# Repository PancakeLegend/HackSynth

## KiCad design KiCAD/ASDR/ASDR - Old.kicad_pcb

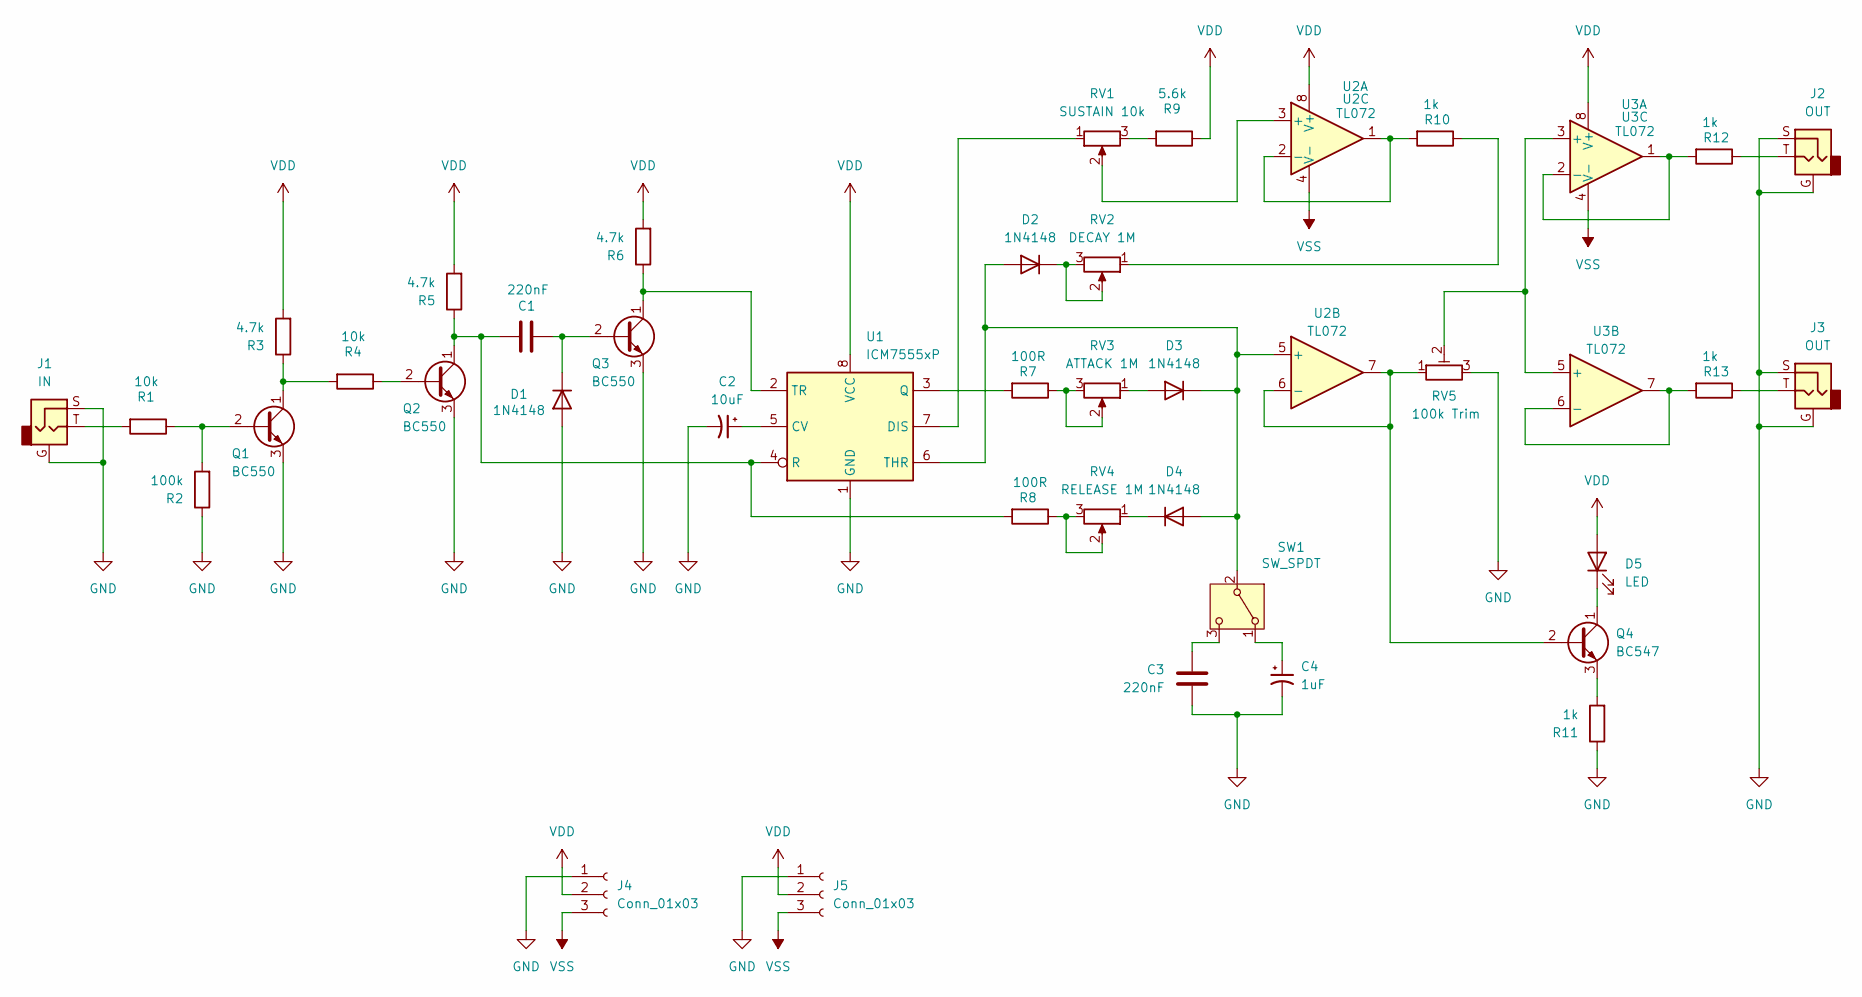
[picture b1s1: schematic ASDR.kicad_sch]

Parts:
C1, C3: 220nF; C_Ceramic_D4.5mm_P5.00mm
C2: 10uF; CP_Radial_D5.2mm_P2.50mm_LayDown
C4: 1uF; C_Ceramic_D4.5mm_P5.00mm
D1, D2, D3, D4: 1N4148; D_DO-35_SOD27_P7.62mm_Horizontal
D5: LED; LED_D5.0mm
J1: IN; Jack_3.5mm
J2, J3: OUT; Jack_3.5mm
J4, J5: Conn_01x03; JST_PH_S3B-PH-K_1x03_P2.00mm_Horizontal
Q1, Q2, Q3: BC550; TO-92_Inline - Handsolder
Q4: BC547; TO-92_Inline - Handsolder
R1, R4: 10k; R_Axial_DIN0207_L6.3mm_D2.5mm_P7.62mm_Horizontal
R2: 100k; R_Axial_DIN0207_L6.3mm_D2.5mm_P7.62mm_Horizontal
R3, R5, R6: 4.7k; R_Axial_DIN0207_L6.3mm_D2.5mm_P7.62mm_Horizontal
R7, R8: 100R; R_Axial_DIN0207_L6.3mm_D2.5mm_P7.62mm_Horizontal
R9: 5.6k; R_Axial_DIN0207_L6.3mm_D2.5mm_P7.62mm_Horizontal
R10, R11, R12, R13: 1k; R_Axial_DIN0207_L6.3mm_D2.5mm_P7.62mm_Horizontal
RV1: SUSTAIN 10k; Potentiometer_Alps_RK09K_Horizontal
RV2: DECAY 1M; Potentiometer_Alps_RK09K_Horizontal
RV3: ATTACK 1M; Potentiometer_Alps_RK09K_Horizontal
RV4: RELEASE 1M; Potentiometer_Alps_RK09K_Horizontal
RV5: 100k Trim; TrimPot_Bourns_3339S_Horizontal
SW1: SW_SPDT; Switch SPDT - MTS-102
U1: ICM7555xP; DIP-8_W7.62mm_LongPads
U2, U3: TL072; DIP-8_W7.62mm_LongPads

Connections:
GND: C2.2, C3.2, C4.2, D1.2 (A), J1.G, J1.S, J2.G, J2.S, J3.G, J3.S, J4.1, J5.1, Q1.3 (E), Q2.3 (E), Q3.3 (E), R2.1, R11.1, RV5.3, U1.1 (GND)
unnamed: C1.1, D1.1 (K), Q3.2 (B)
unnamed: D2.2 (A), D3.1 (K), D4.2 (A), SW1.2 (B), U1.6 (THR), U2.5 (+)
unnamed: D2.1 (K), RV2.2, RV2.3
unnamed: D3.2 (A), RV3.1
unnamed: D4.1 (K), RV4.1
unnamed: D5.1 (K), Q4.1 (C)
unnamed: J1.T, R1.2
unnamed: J2.T, R12.1
unnamed: J3.T, R13.1
unnamed: Q1.2 (B), R1.1, R2.2
unnamed: Q1.1 (C), R3.1, R4.2
unnamed: Q2.2 (B), R4.1
unnamed: C1.2, Q2.1 (C), R5.1, R8.2, U1.4 (R)
unnamed: Q3.1 (C), R6.1, U1.2 (TR)
unnamed: Q4.2 (B), RV5.1, U2.6 (-), U2.7
unnamed: Q4.3 (E), R11.2
unnamed: R7.1, RV3.2, RV3.3
unnamed: R8.1, RV4.2, RV4.3
unnamed: R9.2, RV1.3
unnamed: R10.1, RV2.1
unnamed: C4.1, SW1.1 (A)
unnamed: C3.1, SW1.3 (C)
unnamed: C2.1, U1.5 (CV)
unnamed: RV1.1, U1.7 (DIS)
unnamed: R7.2, U1.3 (Q)
unnamed: RV1.2, U2.3 (+)
unnamed: R10.2, U2.1, U2.2 (-)
unnamed: RV5.2, U3.3 (+), U3.5 (+)
unnamed: R12.2, U3.1, U3.2 (-)
unnamed: R13.2, U3.6 (-), U3.7
VDD: D5.2 (A), J4.2, J5.2, R3.2, R5.2, R6.2, R9.1, U1.8 (VCC), U2.8 (V+), U3.8 (V+)
VSS: J4.3, J5.3, U2.4 (V-), U3.4 (V-)

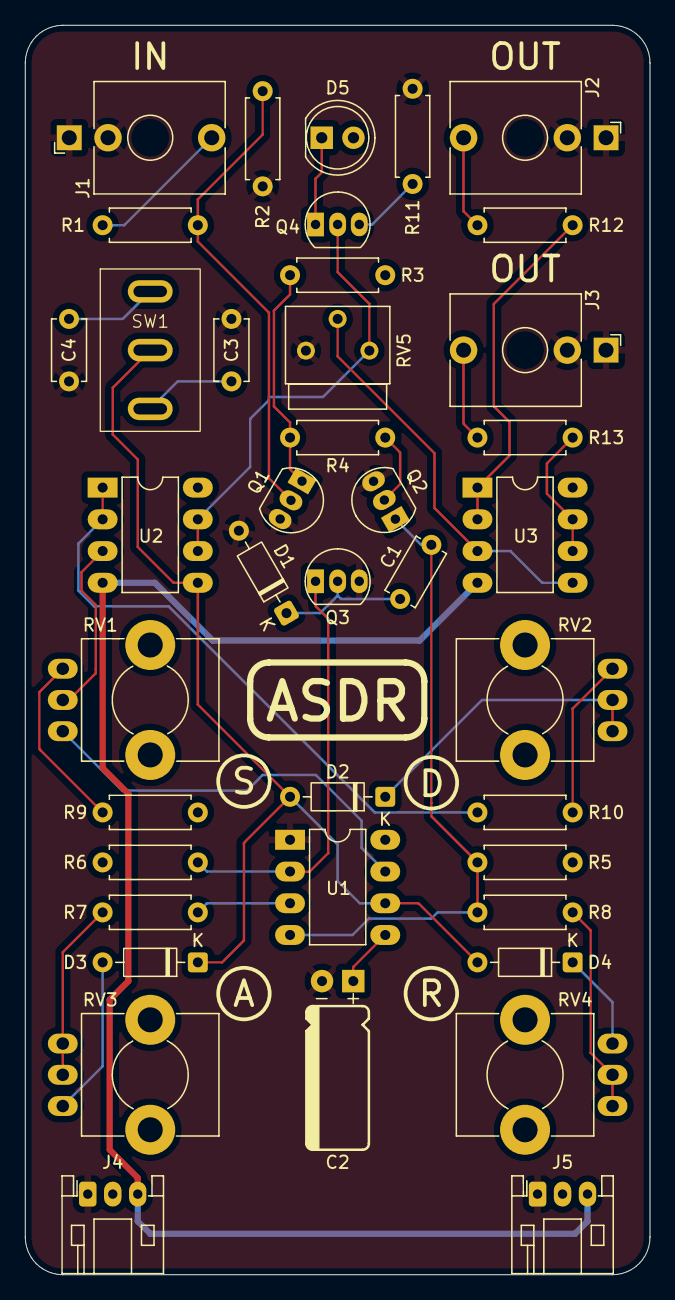
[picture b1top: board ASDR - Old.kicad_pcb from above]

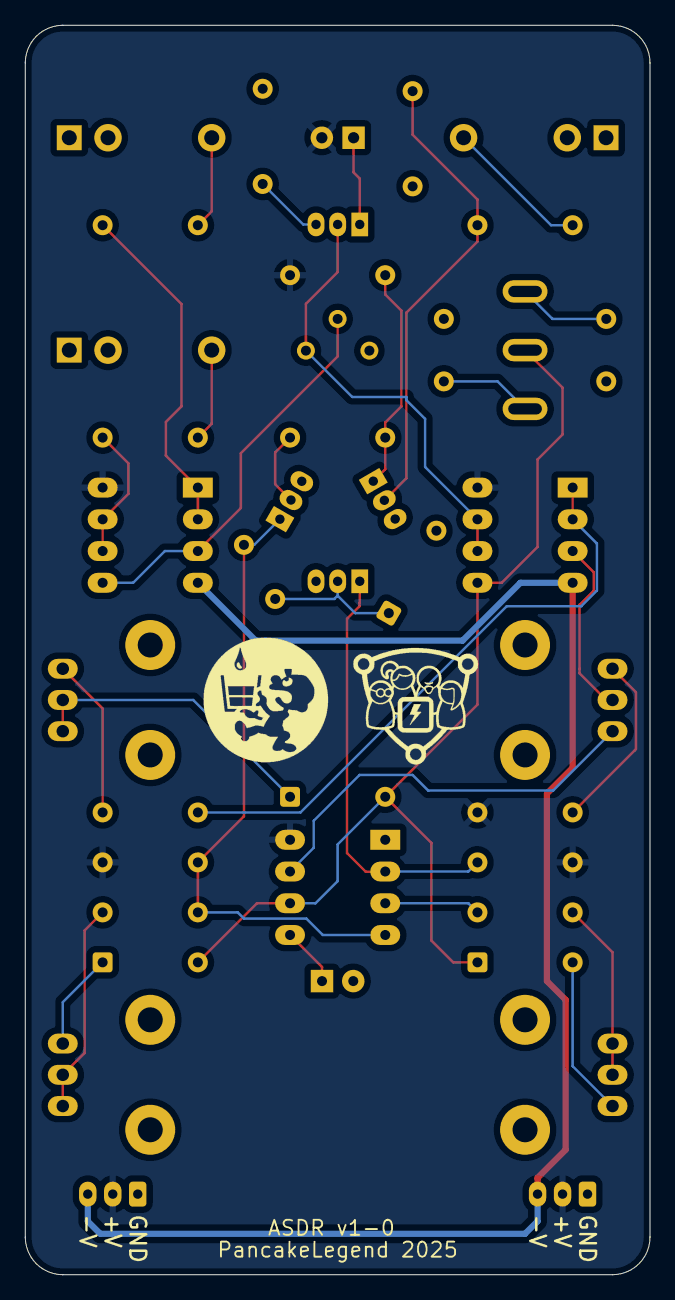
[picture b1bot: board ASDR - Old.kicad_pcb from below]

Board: 2 copper layers, 50.0 x 100.0 mm, 42 parts (2 on the bottom side), 33 nets.

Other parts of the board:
Ref**: Val**; CCHS Logo - 10mm
Ref**#2: Val**; PancakeLegend Logo - 10mm

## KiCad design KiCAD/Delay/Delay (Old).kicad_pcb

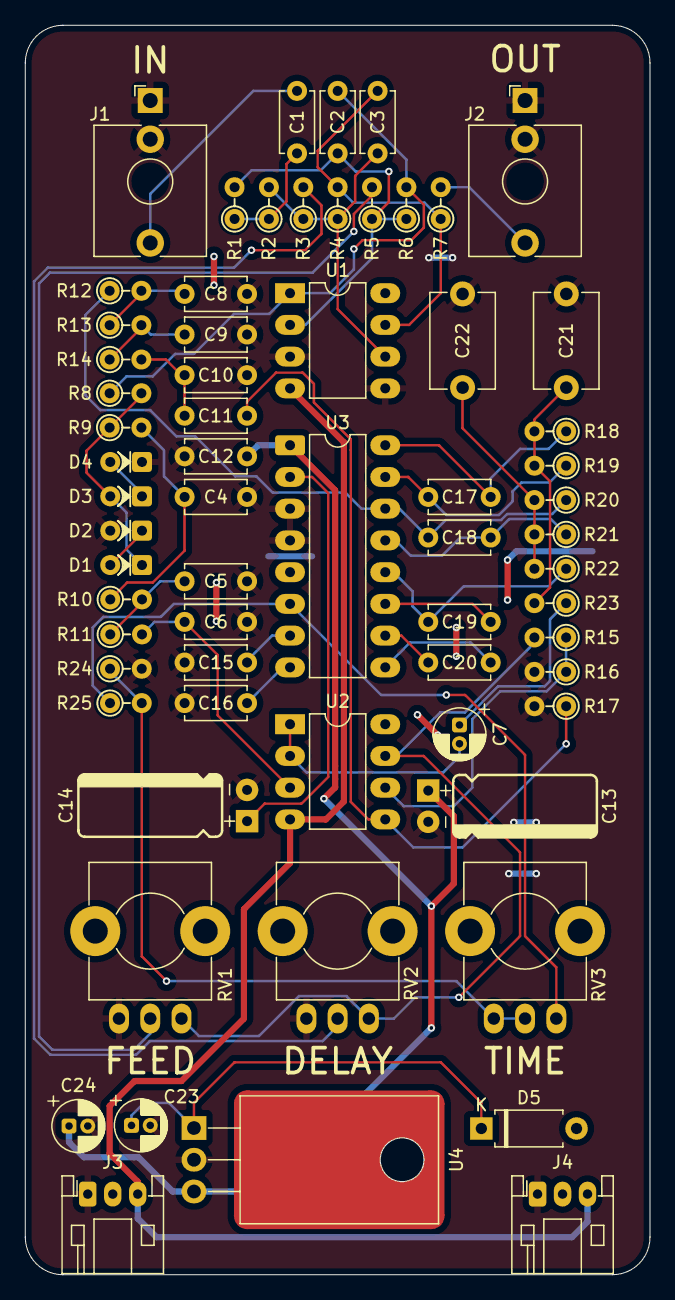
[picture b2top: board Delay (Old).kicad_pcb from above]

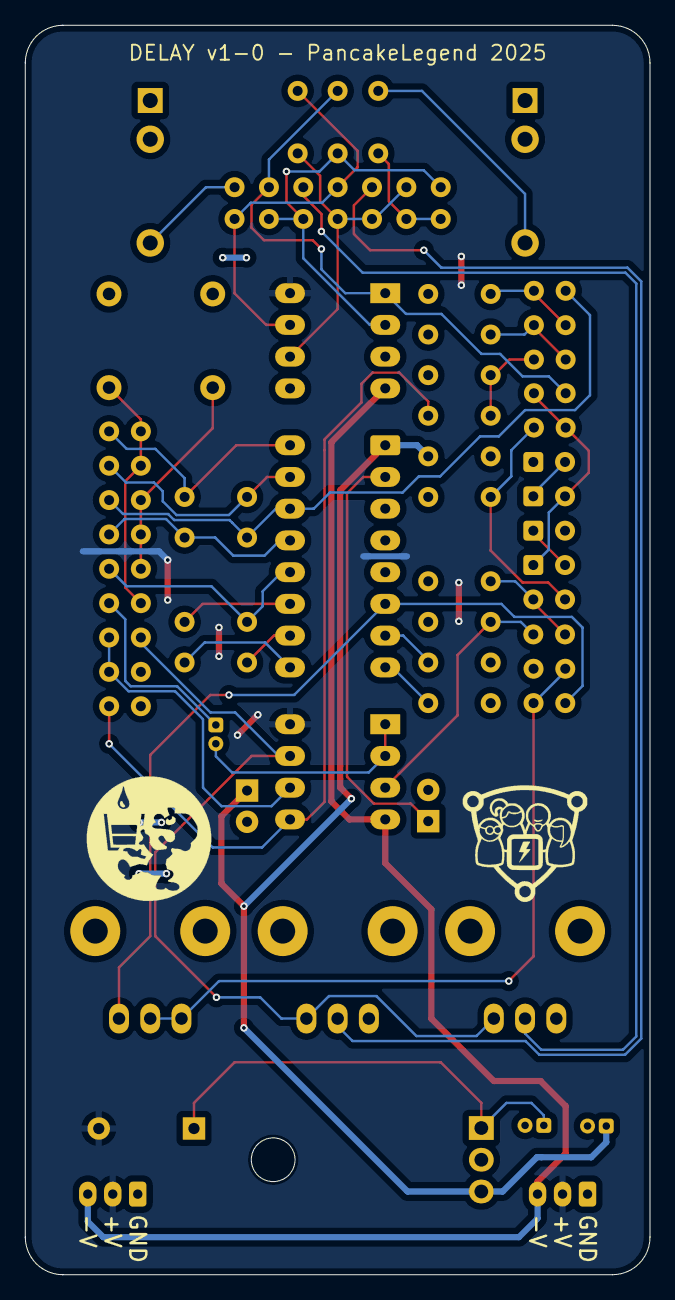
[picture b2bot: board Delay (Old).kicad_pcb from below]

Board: 2 copper layers, 50.0 x 100.0 mm, 67 parts (2 on the bottom side), 43 nets.

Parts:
C1: 220nF; C_Ceramic_D4.5mm_P5.00mm
C2, C3: 68pF; C_Ceramic_D4.5mm_P5.00mm
C4, C8: 2.2nF; C_Ceramic_D4.5mm_P5.00mm
C5, C9: 680pF; C_Ceramic_D4.5mm_P5.00mm
C6, C10: 220pF; C_Ceramic_D4.5mm_P5.00mm
C7: 1uF; CP_Radial_D4.0mm_P1.50mm
C11: 10nF; C_Ceramic_D4.5mm_P5.00mm
C12, C15, C16: 100nF; C_Ceramic_D4.5mm_P5.00mm
C13: 100µF; CP_Radial_D5.2mm_P2.50mm_LayDown
C14: 47µF; CP_Radial_D5.2mm_P2.50mm_LayDown
C17, C18: 560pF; C_Ceramic_D4.5mm_P5.00mm
C19, C20: 22nF; C_Ceramic_D4.5mm_P5.00mm
C21: 6.8nF; C_Disc_D7.5mm_W5.0mm_P7.50mm
C22: 3.3nF; C_Disc_D7.5mm_W5.0mm_P7.50mm
C23: 10uF 25v; CP_Radial_D4.0mm_P1.50mm
C24: 1uF 50v; CP_Radial_D4.0mm_P1.50mm
D1, D2, D3, D4: 1N4148; D_Vertical_P2.54mm
D5: 1N4002; D_A-405_P7.62mm_Horizontal
J1: IN; Jack_3.5mm
J2: OUT; Jack_3.5mm
J3, J4: Conn_01x03; JST_PH_S3B-PH-K_1x03_P2.00mm_Horizontal
R1, R2, R3, R5, R11, R14, R15: 100k; R_Vertical_P2.54mm
R4, R6, R19, R20, R22, R23: 22k; R_Vertical_P2.54mm
R7, R8, R24: 1k; R_Vertical_P2.54mm
R9, R12, R18, R21: 10k; R_Vertical_P2.54mm
R10, R13: 33k; R_Vertical_P2.54mm
R16: 56k; R_Vertical_P2.54mm
R17: 1M; R_Vertical_P2.54mm
R25: 68k; R_Vertical_P2.54mm
RV1, RV2: 10k; Potentiometer_Alps_RK09K_Horizontal
RV3: 47k; Potentiometer_Alps_RK09K_Horizontal
Ref**: Val**; CCHS Logo - 10mm
Ref**#2: Val**; PancakeLegend Logo - 10mm
U1, U2: TL072; DIP-8_W7.62mm_LongPads
U3: PT2399; DIP-16_W7.62mm_LongPads
U4: L7805; L7805 - TO-220-3_Horizontal_TabDown

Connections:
+5V: C12.1, C13.1, C24.1, U3.1 (VCC), U4.3 (OUT)
D IN: C7.1, R23.1
D OUT: C18.1, R12.1, R20.1, U3.14 (LPF2-OUT)
DELAY: R3.2, RV2.2
FEEDBACK: R5.2, RV1.2
GND: C4.2, C5.2, C6.2, C8.2, C9.2, C10.2, C12.2, C13.2, C14.2, C15.2, C16.2, C21.1, C22.1, C23.2, C24.2, D2.1 (K), D4.2 (A), J1.G, J1.S, J2.G, J2.S, J3.1, J4.1, R16.2, R17.2, R24.2, RV1.3, RV2.3, U1.3 (+), U1.5 (+), U3.3 (AGND), U3.4 (DGND), U4.2 (GND)
unnamed: C1.1, R1.1, R2.1
unnamed: C1.2, J1.T
unnamed: C2.1, R6.2, R8.1, U1.1
unnamed: C3.1, R4.2, R7.1, U1.7
unnamed: C4.1, R9.2, R10.1
unnamed: C5.1, R10.2, R11.1
unnamed: C8.1, R12.2, R13.1
unnamed: C9.1, R13.2, R14.1
unnamed: C10.1, C11.1, R14.2
unnamed: C21.2, R18.2, R19.2, R23.2
unnamed: C22.2, R20.2, R21.2, R22.2
unnamed: D1.2 (A), D3.1 (K), R8.2, R9.1
unnamed: D1.1 (K), D2.2 (A)
unnamed: D3.2 (A), D4.1 (K)
unnamed: C23.1, D5.1 (K), U4.1 (IN)
unnamed: J2.T, R7.2
unnamed: R15.2, RV1.1, RV2.1, U2.7
unnamed: R24.1, R25.2, RV3.2, RV3.3
unnamed: C2.2, R1.2, R5.1, R6.1, U1.2 (-)
unnamed: C3.2, R2.2, R3.1, R4.1, U1.6 (-)
unnamed: C6.1, R11.2, U2.3 (+)
unnamed: C7.2, U2.1, U2.2 (-)
unnamed: C11.2, R17.1, U2.5 (+)
unnamed: R15.1, R16.1, U2.6 (-)
unnamed: C16.1, U3.8 (CC0)
unnamed: C15.1, U3.7 (CC1)
unnamed: C17.1, R18.1, U3.16 (LPF1-IN)
unnamed: C17.2, R19.1, U3.15 (LPF1-OUT)
unnamed: C18.2, R21.1, U3.13 (LPF2-IN)
unnamed: C20.1, U3.10 (OP1-IN)
unnamed: C20.2, U3.9 (OP1-OUT)
unnamed: C19.2, U3.11 (OP2-IN)
unnamed: C19.1, R22.1, U3.12 (OP2-OUT)
unnamed: C14.1, U3.2 (REF)
TIME: R25.1, RV3.1, U3.6 (VCO)
VDD: D5.2 (A), J3.2, J4.2, U1.8 (V+), U2.8 (V+)
VSS: J3.3, J4.3, U1.4 (V-), U2.4 (V-)

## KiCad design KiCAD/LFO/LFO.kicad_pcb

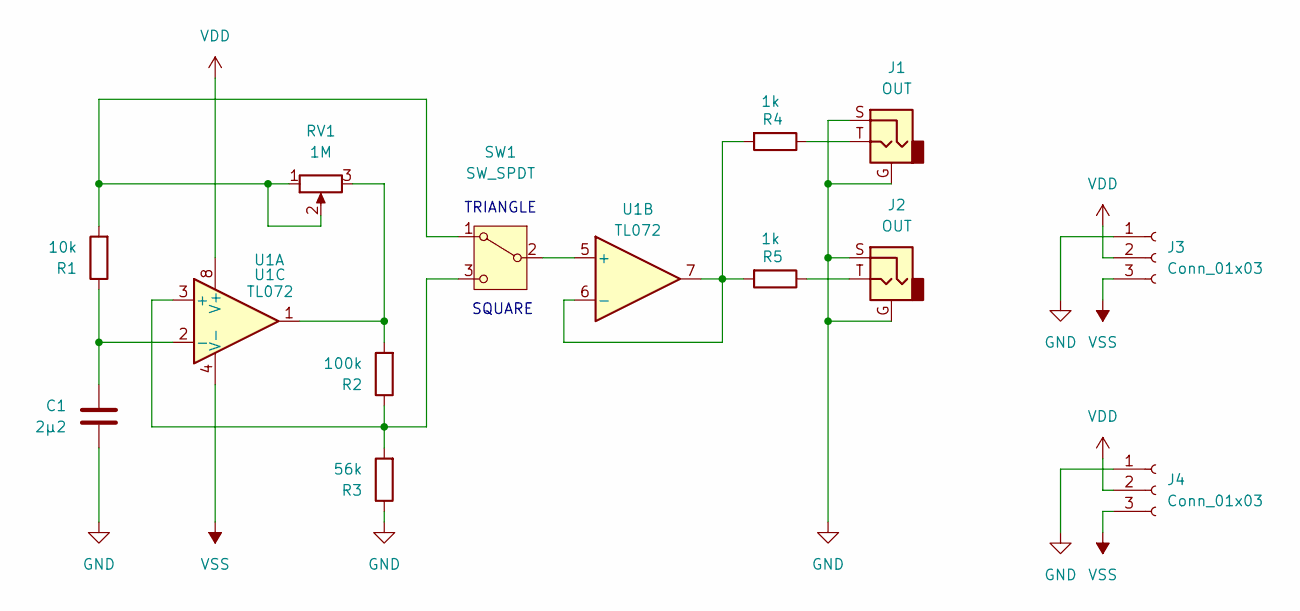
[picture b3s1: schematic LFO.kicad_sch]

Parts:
C1: 2µ2; C_Ceramic_D4.5mm_P5.00mm
J1, J2: OUT; Jack_3.5mm
J3, J4: Conn_01x03; JST_PH_S3B-PH-K_1x03_P2.00mm_Horizontal
R1: 10k; R_Axial_DIN0207_L6.3mm_D2.5mm_P7.62mm_Horizontal
R2: 100k; R_Axial_DIN0207_L6.3mm_D2.5mm_P7.62mm_Horizontal
R3: 56k; R_Axial_DIN0207_L6.3mm_D2.5mm_P7.62mm_Horizontal
R4, R5: 1k; R_Axial_DIN0207_L6.3mm_D2.5mm_P7.62mm_Horizontal
RV1: 1M; Potentiometer_Alps_RK09K_Horizontal
SW1: SW_SPDT; Switch SPDT - MTS-102
U1: TL072; DIP-8_W7.62mm_LongPads

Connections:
GND: C1.2, J1.G, J1.S, J2.G, J2.S, J3.1, J4.1, R3.1
unnamed: J1.T, R4.1
unnamed: J2.T, R5.1
unnamed: R2.2, RV1.3, U1.1
unnamed: R1.2, RV1.1, RV1.2, SW1.1 (A)
unnamed: SW1.2 (B), U1.5 (+)
unnamed: R2.1, R3.2, SW1.3 (C), U1.3 (+)
unnamed: C1.1, R1.1, U1.2 (-)
unnamed: R4.2, R5.2, U1.6 (-), U1.7
VDD: J3.2, J4.2, U1.8 (V+)
VSS: J3.3, J4.3, U1.4 (V-)

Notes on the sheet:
SQUARE
TRIANGLE

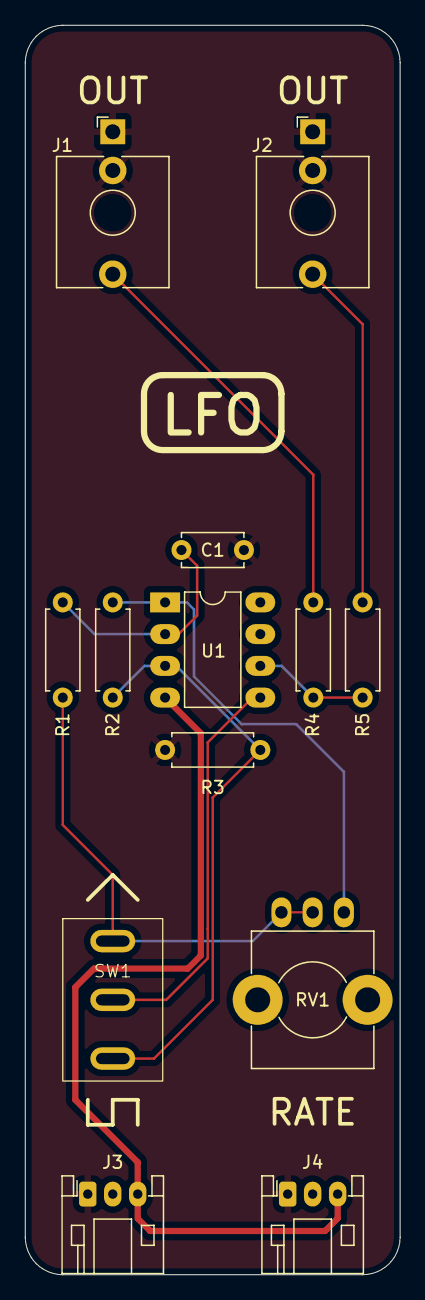
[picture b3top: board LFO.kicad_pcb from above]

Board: 2 copper layers, 30.0 x 100.0 mm, 14 parts (1 on the bottom side), 11 nets.

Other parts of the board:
Ref**: Val**; CCHS Logo - 10mm

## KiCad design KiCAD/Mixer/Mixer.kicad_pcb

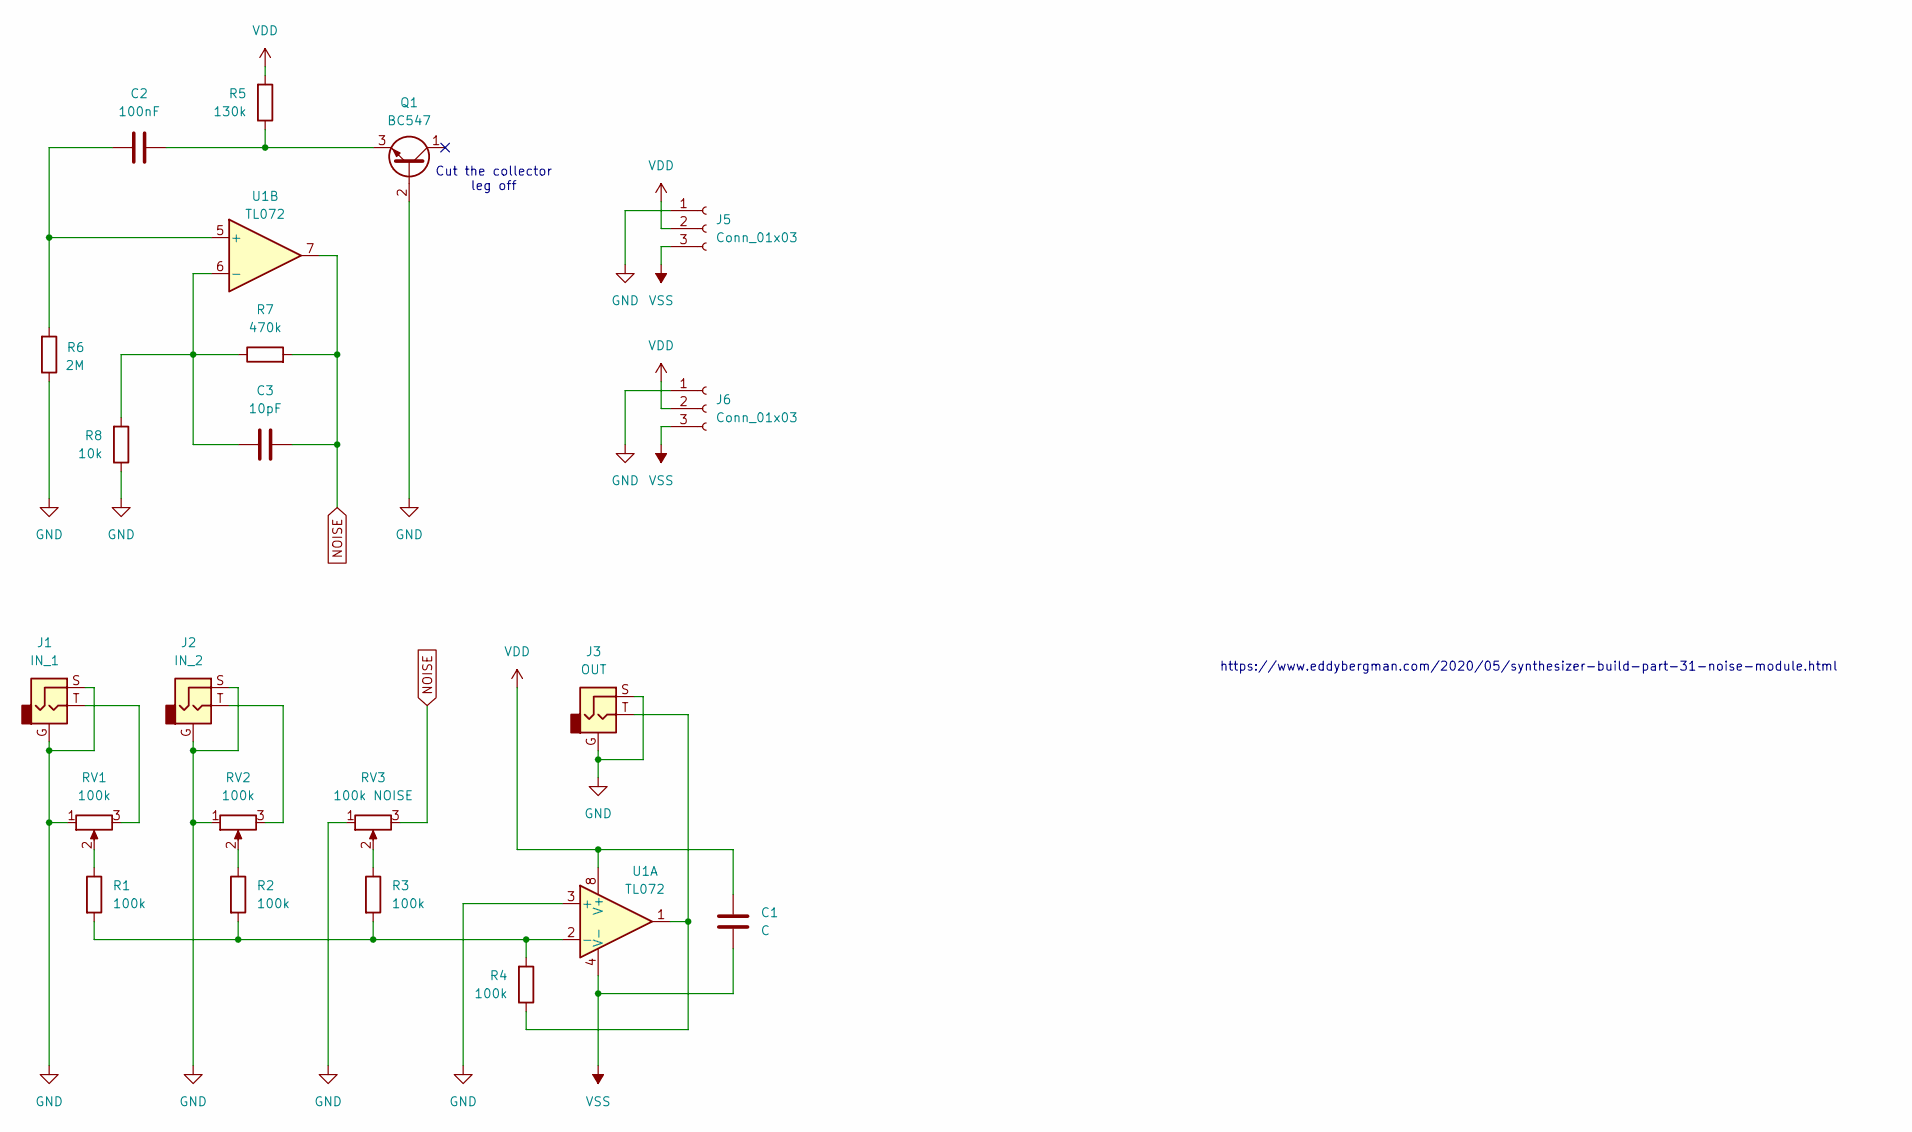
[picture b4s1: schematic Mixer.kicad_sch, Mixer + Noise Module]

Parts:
C1: C; C_Disc_D5.0mm_W2.5mm_P5.00mm
C2: 100nF; C_Disc_D5.0mm_W2.5mm_P5.00mm
C3: 10pF; C_Disc_D5.0mm_W2.5mm_P5.00mm
J1: IN_1; Jack_3.5mm
J2: IN_2; Jack_3.5mm
J3: OUT; Jack_3.5mm
J5, J6: Conn_01x03; JST_PH_S3B-PH-K_1x03_P2.00mm_Horizontal
Q1: BC547; TO-92_Inline - BC547 - 2-Pin Handsolder
R1, R2, R3, R4: 100k; R_Axial_DIN0207_L6.3mm_D2.5mm_P7.62mm_Horizontal
R5: 130k; R_Axial_DIN0207_L6.3mm_D2.5mm_P7.62mm_Horizontal
R6: 2M; R_Axial_DIN0207_L6.3mm_D2.5mm_P7.62mm_Horizontal
R7: 470k; R_Axial_DIN0207_L6.3mm_D2.5mm_P7.62mm_Horizontal
R8: 10k; R_Axial_DIN0207_L6.3mm_D2.5mm_P7.62mm_Horizontal
RV1, RV2: 100k; Potentiometer_Alps_RK09K_Horizontal
RV3: 100k NOISE; Potentiometer_Alps_RK09K_Horizontal
U1: TL072; DIP-8_W7.62mm_LongPads

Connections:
GND: J1.G, J1.S, J2.G, J2.S, J3.G, J3.S, J5.1, J6.1, Q1.2 (B), R6.1, R8.1, RV1.1, RV2.1, RV3.1, U1.3 (+)
NOISE: C3.2, R7.2, RV3.3, U1.7
unnamed: J1.T, RV1.3
unnamed: J2.T, RV2.3
unnamed: J3.T, R4.1, U1.1
unnamed: C2.2, Q1.3 (E), R5.1
unnamed: R1.1, RV1.2
unnamed: R2.1, RV2.2
unnamed: R3.1, RV3.2
unnamed: R1.2, R2.2, R3.2, R4.2, U1.2 (-)
unnamed: C2.1, R6.2, U1.5 (+)
unnamed: C3.1, R7.1, R8.2, U1.6 (-)
VDD: C1.1, J5.2, J6.2, R5.2, U1.8 (V+)
VSS: C1.2, J5.3, J6.3, U1.4 (V-)

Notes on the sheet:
https://www.eddybergman.com/2020/05/synthesizer-build-part-31-noise-module.html
Cut the collector leg off

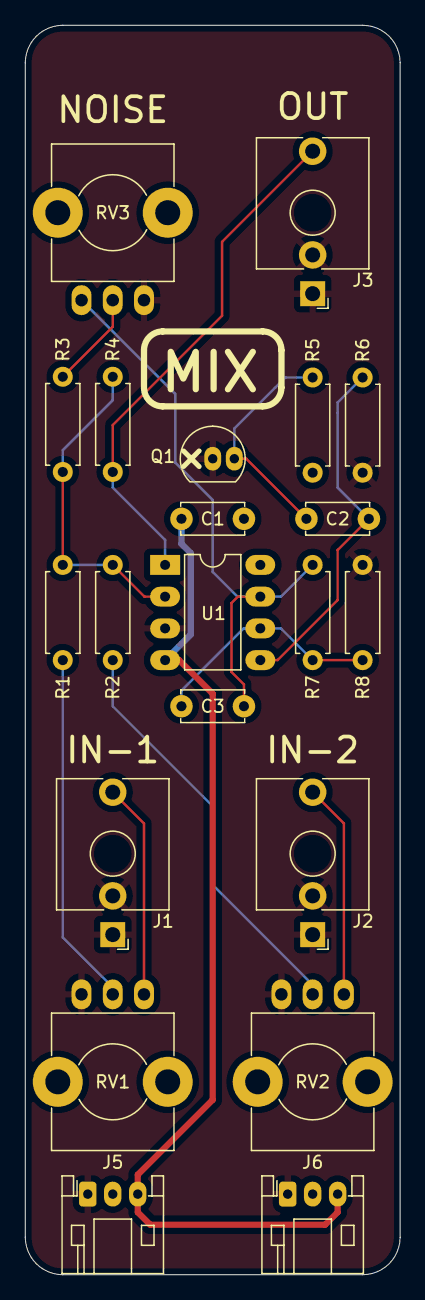
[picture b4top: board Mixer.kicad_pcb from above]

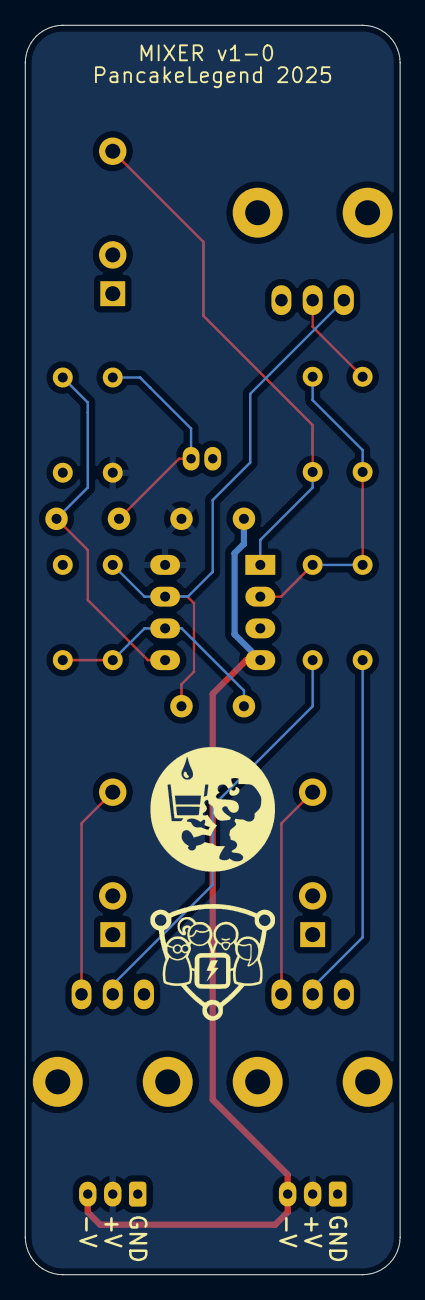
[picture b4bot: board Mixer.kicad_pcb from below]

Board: 2 copper layers, 30.0 x 100.0 mm, 23 parts (2 on the bottom side), 14 nets.

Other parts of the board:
Ref**: Val**; CCHS Logo - 10mm
Ref**#2: Val**; PancakeLegend Logo - 10mm

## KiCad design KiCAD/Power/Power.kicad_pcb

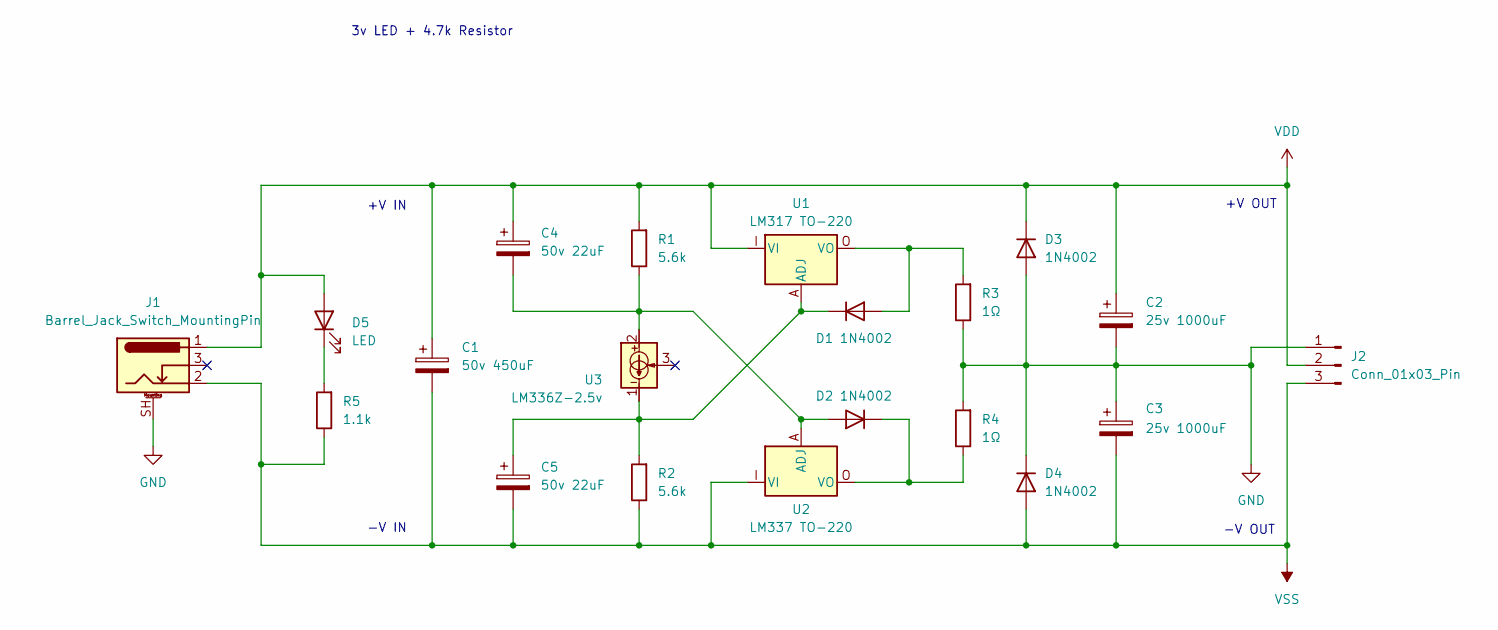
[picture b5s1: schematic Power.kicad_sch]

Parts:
C1: 50v 450uF; CP_Radial_D10.0mm_P5.00mm_MidMount
C2, C3: 25v 1000uF; CP_Radial_D10.0mm_P5.00mm_MidMount
C4, C5: 50v 22uF; CP_Radial_D5.2mm_P2.50mm_LayDown
D1, D2, D3, D4: 1N4002; D_A-405_P7.62mm_Horizontal
D5: LED; LED_D5.0mm
J1: Barrel_Jack_Switch_MountingPin; BarrelJack_DC044A
J2: Conn_01x03_Pin; JST_PH_S3B-PH-K_1x03_P2.00mm_Horizontal
R1, R2: 5.6k; R_Axial_DIN0207_L6.3mm_D2.5mm_P7.62mm_Horizontal
R3, R4: 1Ω; R_Axial_DIN0207_L6.3mm_D2.5mm_P7.62mm_Horizontal
R5: 1.1k; R_Axial_DIN0207_L6.3mm_D2.5mm_P7.62mm_Horizontal
U1: LM317 TO-220; LM317 - TO-220-3_Horizontal_TabDown
U2: LM337 TO-220; LM337 - TO-220-3_Horizontal_TabDown
U3: LM336Z-2.5v; TO-92_Inline - Handsolder

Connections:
GND: C2.2, C3.1, D3.2 (A), D4.1 (K), J1.SH (MountPin), J2.1, R3.1, R4.2
unnamed: D1.2 (A), R3.2, U1.O (VO)
unnamed: C5.1, D1.1 (K), R2.2, U1.A (ADJ), U3.1
unnamed: C4.2, D2.2 (A), R1.1, U2.A (ADJ), U3.2
unnamed: D2.1 (K), R4.1, U2.O (VO)
unnamed: D5.1 (K), R5.2
VDD: C1.1, C2.1, C4.1, D3.1 (K), D5.2 (A), J1.1, J2.2, R1.2, U1.I (VI)
VSS: C1.2, C3.2, C5.2, D4.2 (A), J1.2, J2.3, R2.1, R5.1, U2.I (VI)

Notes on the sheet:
3v LED + 4.7k Resistor
-V OUT
+V OUT
-V IN
+V IN

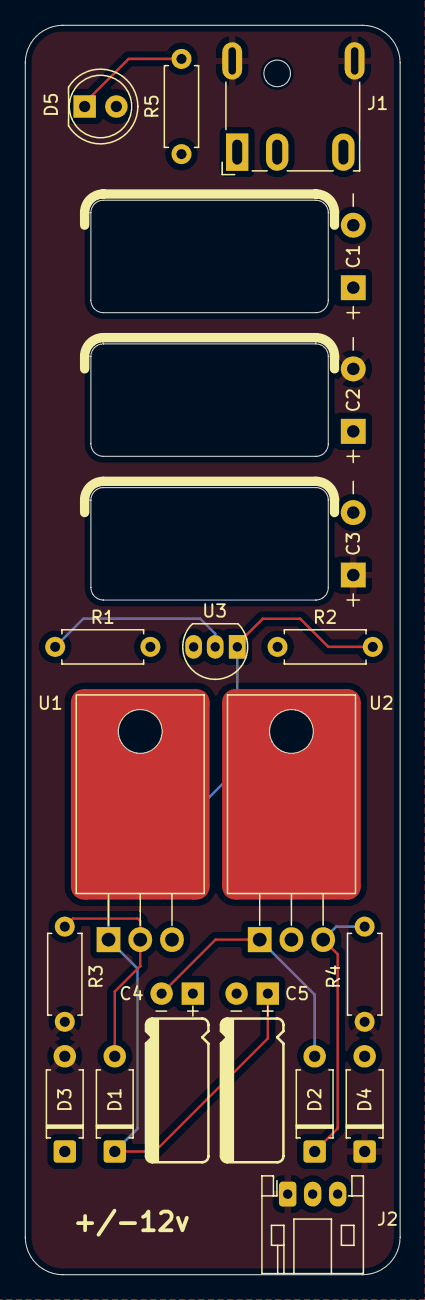
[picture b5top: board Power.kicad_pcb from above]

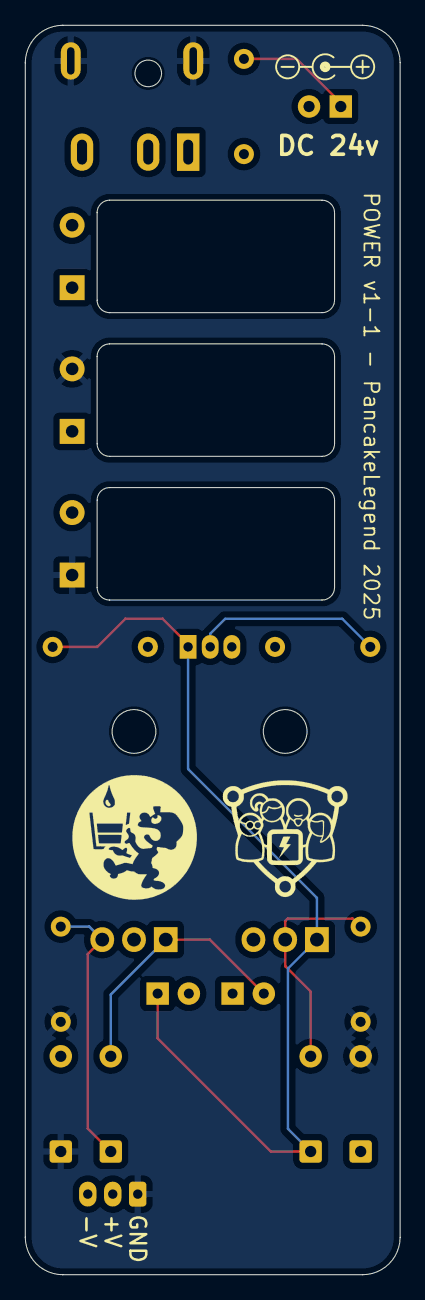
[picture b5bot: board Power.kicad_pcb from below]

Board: 4 copper layers, 30.0 x 100.0 mm, 22 parts (2 on the bottom side), 8 nets.

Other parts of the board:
Ref**: Val**; PancakeLegend Logo - 10mm
Ref**#2: Val**; CCHS Logo - 10mm
